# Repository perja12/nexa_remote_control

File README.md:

# Nexa remote control

Hardware and firmware for creating custom Nexa remote control. This project uses ATtiny85 and a STX882 ASK module as the RF module. It can be used to control various Nexa devices that uses 433 MHz.

One of the goals was to minimize the power usage so that it can run from a battery like CR2032.

## Installing NexaCtrl library

The firmware uses the NexaCtrl library and this be installed in your Arduino folder:
```bash
cd ~/Arduino/libraries
git clone git@github.com:calle-gunnarsson/NexaCtrl.git
```

## Building the firmware and uploading it to ATtiny85

To build the firmware, use the provided Makefile:
```bash
make
```

This project uses an Arduino Uno to program the ATtiny85:
https://create.arduino.cc/projecthub/arjun/programming-attiny85-with-arduino-uno-afb829

Once you have the setup ready you can upload the firmware with the command:
```bash
make upload
```

# Hardware

See the hardware folder for schematic and board layout files from Eagle. And also the list of parts. Note that it can use either a coin cell battery (CR2032) or f.ex. 2xAA batteries connected to the battery terminal.

The RF module used here is https://www.aliexpress.com/item/10pcs-lot-ASK-RF-module-433mhz-transmitter-module/32238392004.html

# Resources
* Nexa devices: https://www.nexa.se/vara-produkter/system-nexa/mottagare-paav
* Pin change interrupt on ATtiny85:
    * https://thewanderingengineer.com/2014/08/11/pin-change-interrupts-on-attiny85/
    * https://embeddedthoughts.com/2016/06/06/attiny85-introduction-to-pin-change-and-timer-interrupts/
    * http://gammon.com.au/interrupts
* ATtiny85 datasheet: http://www.atmel.com/images/atmel-2586-avr-8-bit-microcontroller-attiny25-attiny45-attiny85_datasheet.pdf
* NexaCtrl library: https://github.com/calle-gunnarsson/NexaCtrl

# How to pair with a Nexa device

In order to use the controller with a device (like a plug-in receiver) you need to either find the existing id of your device and use that in `CONTROLLER_ID`. Or you can configure the device to listen for the id set in `CONTROLLER_ID` (self learning). Disconnect the device from mains and then plug it back in. Then, within 5 seconds, press the "on" button on the controller. You should then hear the relay switching a couple of times. If nothing happens, the device memory can be full and you have to reset it with a "group off" command during that 5 seconds start up. You probably have to do this with a paired remote. Consult the user manual of the device.

# Questions or found a bug?

Please raise an [issue](https://github.com/perja12/nexa_remote_control/issues/new) or a new [pull request](https://github.com/perja12/nexa_remote_control/pulls) if you have some code changes.

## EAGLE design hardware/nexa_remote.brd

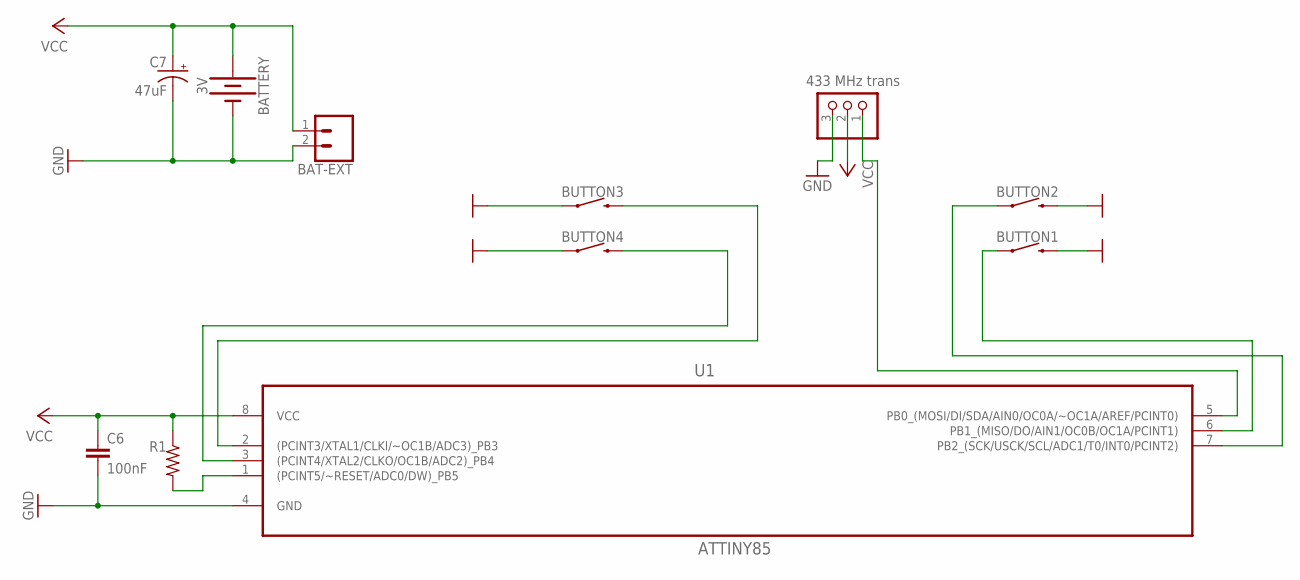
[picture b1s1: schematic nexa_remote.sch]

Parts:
BAT-EXT: CONN_023.5MM; SCREWTERMINAL-3.5MM-2
BATTERY: 3V; BATTCON_20MM_4LEGS
BUTTON1, BUTTON2, BUTTON3, BUTTON4: MOMENTARY-SWITCH-SPST-PTH-6.0MM; TACTILE_SWITCH_PTH_6.0MM
C6: 100nF; 0805
C7: 47uF; CPOL-RADIAL-2.5MM-5MM
JMR-TX-1: 433 MHz trans; 1X03-CLEANBIG
R1: 10K; 0805
U1: ATTINY85; DIP254P762X533-8

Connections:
GND: BAT-EXT.2, BATTERY.NEGATIVE (-), BUTTON1.3 (2), BUTTON2.3 (2), BUTTON3.1, BUTTON4.1, C6.2, C7.2 (-), JMR-TX-1.3, U1.4 (GND)
unnamed: R1.2, U1.1 ((PCINT5/~RESET/ADC0/DW)_PB5)
unnamed: JMR-TX-1.1, U1.5 (PB0_(MOSI/DI/SDA/AIN0/OC0A/~OC1A/AREF/P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)
unnamed: BUTTON1.1, U1.6 (PB1_(MISO/DO/AIN1/OC0B/OC1A/PCINT1))
unnamed: BUTTON3.3 (2), U1.2 ((PCINT3/XTAL1/CLKI/~OC1B/ADC3)_PB3)
unnamed: BUTTON4.3 (2), U1.3 ((PCINT4/XTAL2/CLKO/OC1B/ADC2)_PB4)
unnamed: BUTTON2.1, U1.7 (PB2_(SCK/USCK/SCL/ADC1/T0/INT0/PCINT2))
VCC: BAT-EXT.1, BATTERY.POSITIVE@1 (+), BATTERY.POSITIVE@2 (+), BATTERY.POSITIVE@3 (+), BATTERY.POSITIVE@4 (+), C6.1, C7.1 (+), JMR-TX-1.2, R1.1, U1.8 (VCC)

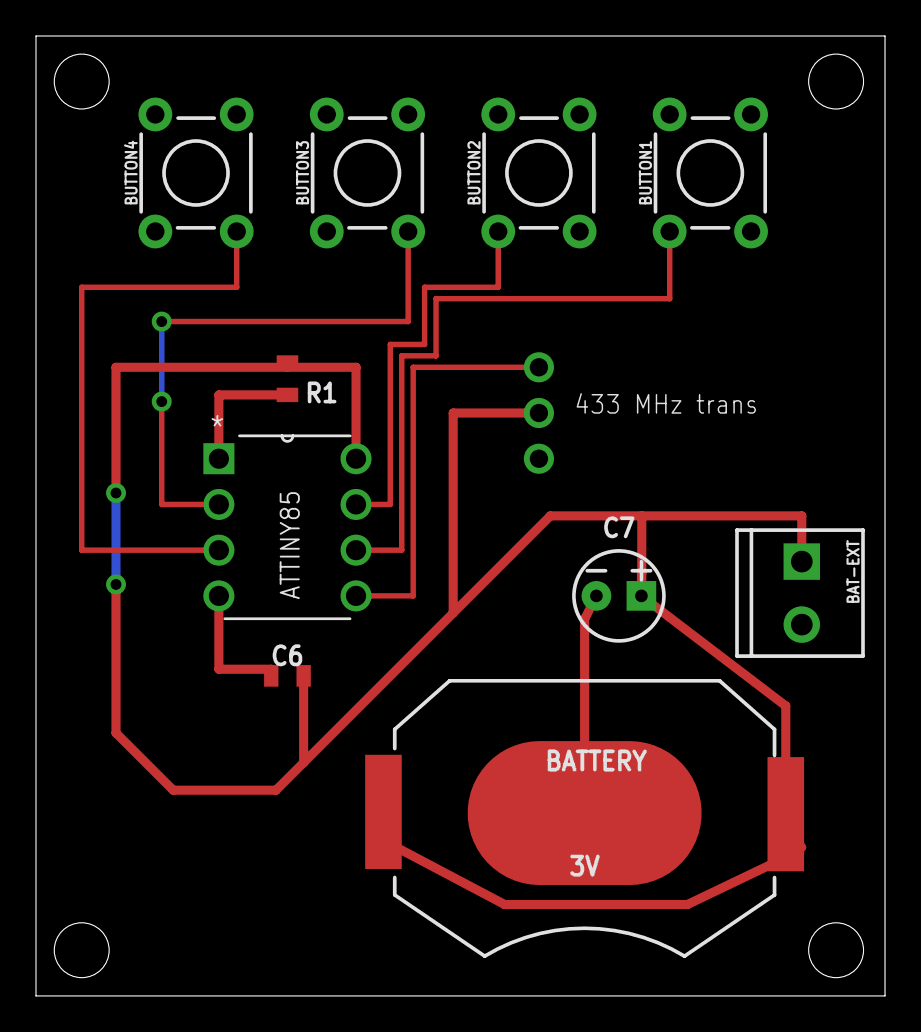
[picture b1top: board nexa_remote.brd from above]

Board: 2 copper layers, 47.2 x 53.3 mm, 11 parts (0 on the bottom side), 8 nets.

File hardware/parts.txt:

Part     Value          Device                          Package                  Library                       Sheet

BAT-EXT                 CONN_023.5MM                    SCREWTERMINAL-3.5MM-2    SparkFun-Connectors           1
BATTERY  3V             BATTERY-20MM_SMD_4LEGS          BATTCON_20MM_4LEGS       SparkFun-Batteries            1
BUTTON1                 MOMENTARY-SWITCH-SPST-PTH-6.0MM TACTILE_SWITCH_PTH_6.0MM SparkFun-Switches             1
BUTTON2                 MOMENTARY-SWITCH-SPST-PTH-6.0MM TACTILE_SWITCH_PTH_6.0MM SparkFun-Switches             1
BUTTON3                 MOMENTARY-SWITCH-SPST-PTH-6.0MM TACTILE_SWITCH_PTH_6.0MM SparkFun-Switches             1
BUTTON4                 MOMENTARY-SWITCH-SPST-PTH-6.0MM TACTILE_SWITCH_PTH_6.0MM SparkFun-Switches             1
C6       100nF          0.33UF/330NF-0805-50V-10%       0805                     SparkFun-Capacitors           1
C7       47uF           10UF-POLAR-RADIAL-2.5MM-25V-20% CPOL-RADIAL-2.5MM-5MM    SparkFun-Capacitors           1
JMR-TX-1 433 MHz trans  PINHD-1X3CB                     1X03-CLEANBIG            adafruit                      1
R1       10K            0.3OHM-0805-1/8W-1%             0805                     SparkFun-Resistors            1
U1       ATTINY85       ATTINY85-20PU                   DIP254P762X533-8         Atmel_By_element14_Batch_1-00 1

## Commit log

2018-03-28 New firmware for version 1.1 and updated instructions.
2018-03-28 Fix markdown and use jpg.
2018-03-28 Add link to RF module.
2018-03-28 Update readme.
2018-03-29 Updated readme with pairing info.
2018-04-08 Add image of final circuit.
2018-04-08 Remove width attribute (not working).

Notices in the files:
parts and their libraries:
SparkFun-Batteries: Licensing: Creative Commons ShareAlike 4.0 International - https://creativecommons.org/licenses/by-sa/4.0
